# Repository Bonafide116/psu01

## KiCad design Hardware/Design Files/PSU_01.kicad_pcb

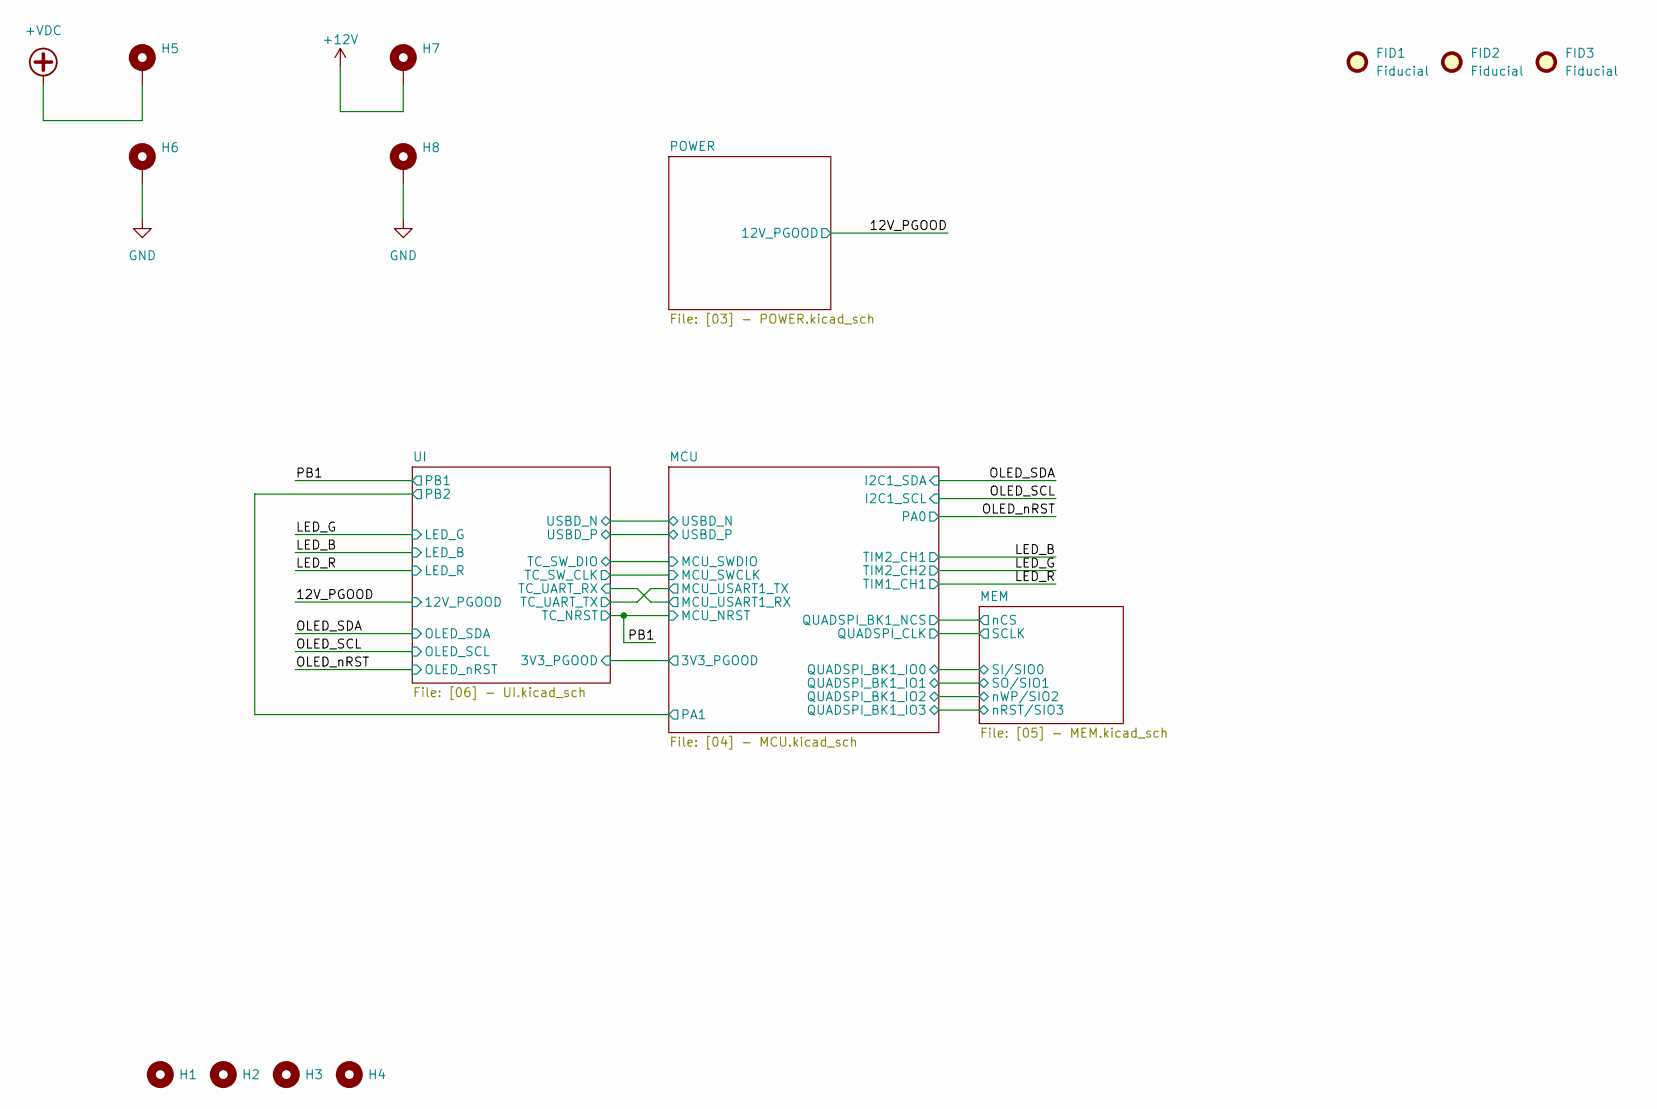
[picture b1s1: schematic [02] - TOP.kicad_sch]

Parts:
FID1, FID2, FID3: Fiducial; FID
H1, H2, H3, H4: MountingHole; MountingHole_3.5mm_Pad_Via
H5, H6, H7, H8: MountingHole_Pad; MountingHole_2.7mm_Pad

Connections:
+12V: H7.1; also elsewhere on the board
+VDC: H5.1; also elsewhere on the board
GND: H6.1, H8.1; also elsewhere on the board

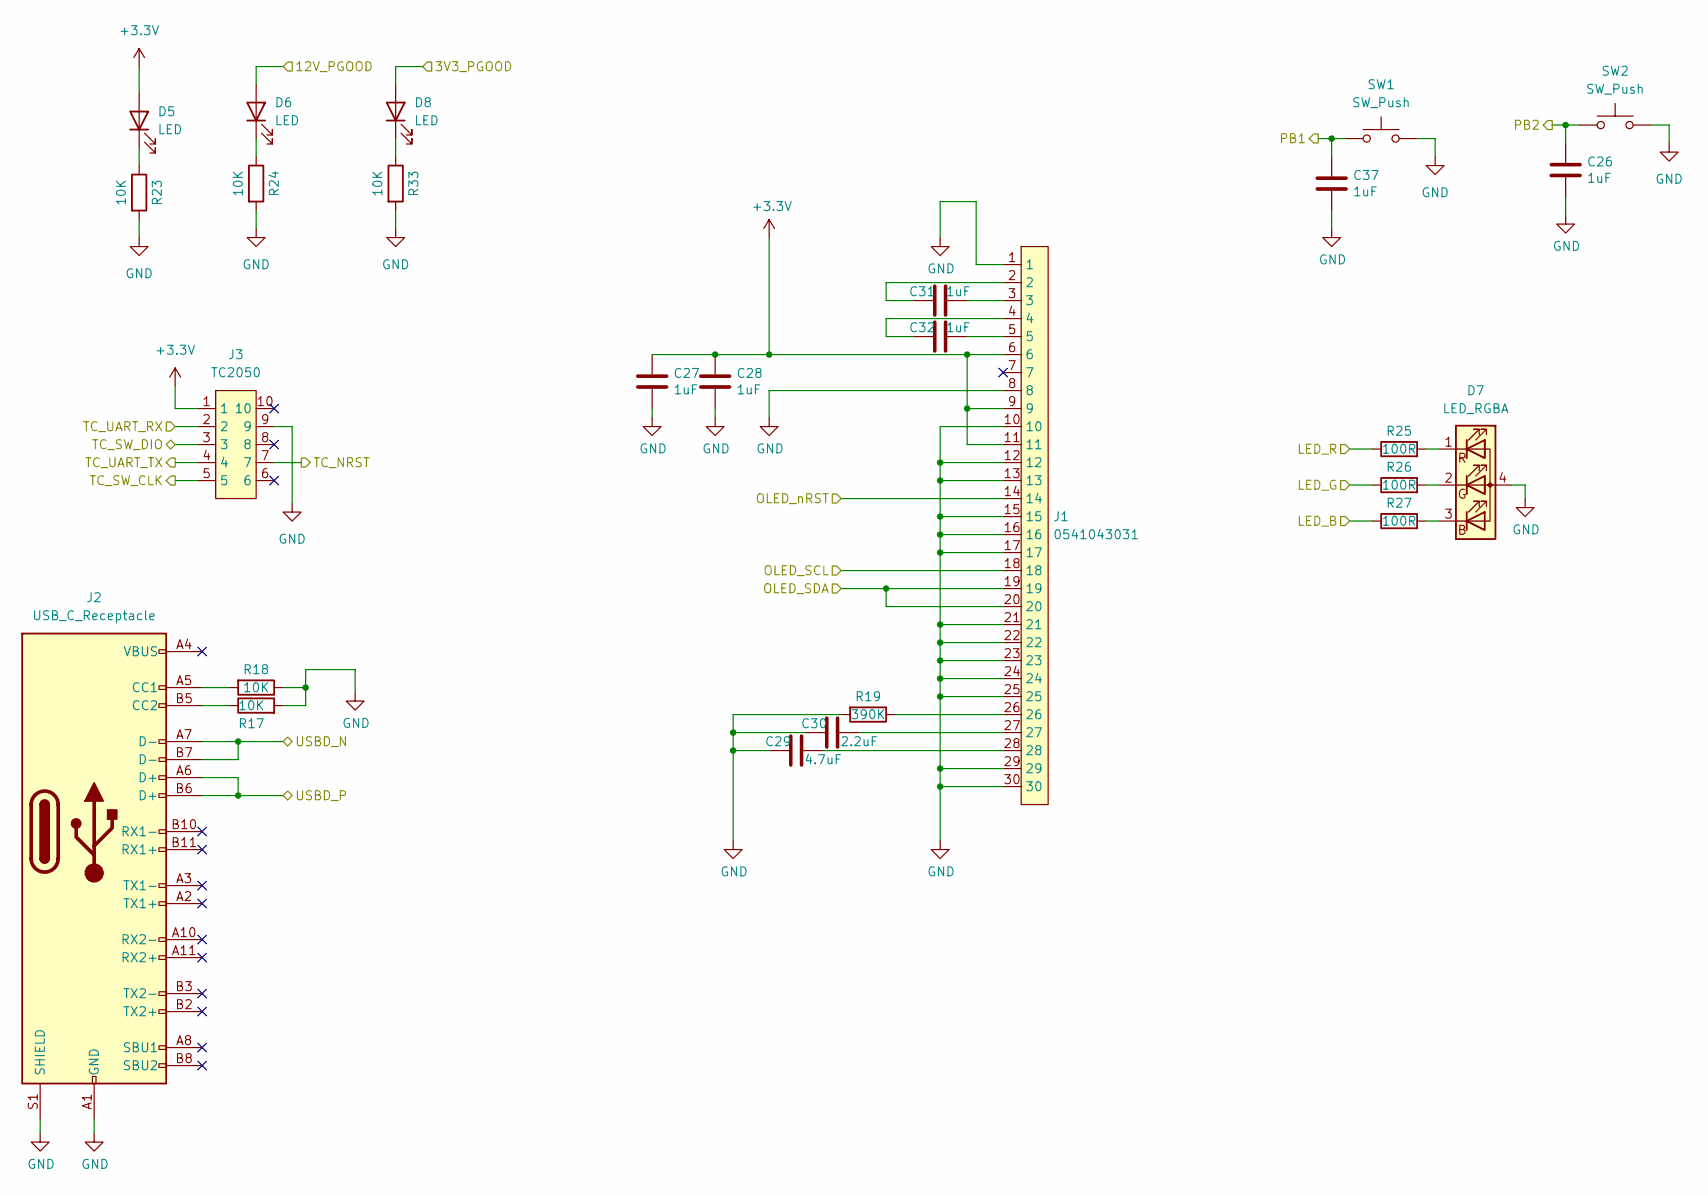
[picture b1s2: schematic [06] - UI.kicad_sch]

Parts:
C26, C27, C28, C31, C32, C37: 1uF; C_0603_1608Metric; Part Number CL10B105KP8NNNC
C29: 4.7uF; C_0603_1608Metric; Part Number CL10A475KO8NNNC
C30: 2.2uF; C_0603_1608Metric; Part Number CL10A225KO8NNNC
D5, D6, D8: LED; LED_0603_1608Metric
D7: LED_RGBA; LTST-C19HE1WT; Part Number LTST-C19HE1WT
J1: 0541043031; Part Number 0541043031
J2: USB_C_Receptacle; USB_C_Receptacle_Molex_105450-0101; Part Number 1054500101
J3: TC2050; Tag-Connect_TC2050-IDC-FP_2x05_P1.27mm_Vertical
R17, R18, R23, R24, R33: 10K; R_0603_1608Metric; Part Number RC0603FR-0710KL
R19: 390K; R_0603_1608Metric; Part Number RC0603FR-07390KL
R25, R26, R27: 100R; R_0603_1608Metric; Part Number RC0603FR-07100RL
SW1, SW2: SW_Push; SW_Push_1P1T_NO_Vertical_Wuerth_434133025816; Part Number 434133025816

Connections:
+3.3V: C27.2, C28.2, D5.2 (A), J1.6, J1.9, J1.11, J3.1; also elsewhere on the board
/TOP/12V_PGOOD: D6.2 (A); also elsewhere on the board
/TOP/LED_B: R27.1; also elsewhere on the board
/TOP/LED_G: R26.1; also elsewhere on the board
/TOP/LED_R: R25.1; also elsewhere on the board
/TOP/MCU/3V3_PGOOD: D8.2 (A); also elsewhere on the board
/TOP/MCU/MCU_SWCLK: J3.5; also elsewhere on the board
/TOP/MCU/MCU_SWDIO: J3.3; also elsewhere on the board
/TOP/MCU/MCU_USART1_RX: J3.2; also elsewhere on the board
/TOP/MCU/MCU_USART1_TX: J3.4; also elsewhere on the board
/TOP/MCU/PA1: C26.2, SW2.1; also elsewhere on the board
/TOP/MCU/USBD_N: J2.A7 (D-), J2.B7 (D-); also elsewhere on the board
/TOP/MCU/USBD_P: J2.A6 (D+), J2.B6 (D+); also elsewhere on the board
/TOP/OLED_SCL: J1.18; also elsewhere on the board
/TOP/OLED_SDA: J1.19, J1.20; also elsewhere on the board
/TOP/OLED_nRST: J1.14; also elsewhere on the board
/TOP/PB1: C37.2, J3.7, SW1.1; also elsewhere on the board
GND: C26.1, C27.1, C28.1, C29.2, C30.2, C37.1, D7.4 (A), J1.1, J1.8, J1.10, J1.12, J1.13, J1.15, J1.16, J1.17, J1.21, J1.22, J1.23, J1.24, J1.25, J1.29, J1.30, J2.A1 (GND), J2.A12 (GND), J2.B1 (GND), J2.B12 (GND), J2.S1 (SHIELD), J3.9, R17.2, R18.1, R19.2, R23.2, R24.2, R33.2, SW1.2, SW2.2; also elsewhere on the board
unnamed: C29.1, J1.28
unnamed: C30.1, J1.27
unnamed: C31.1, J1.3
unnamed: C31.2, J1.2
unnamed: C32.1, J1.5
unnamed: C32.2, J1.4
unnamed: D5.1 (K), R23.1
unnamed: D6.1 (K), R24.1
unnamed: D7.1 (RK), R25.2
unnamed: D7.2 (GK), R26.2
unnamed: D7.3 (BK), R27.2
unnamed: D8.1 (K), R33.1
unnamed: J1.26, R19.1
unnamed: J2.A5 (CC1), R18.2
unnamed: J2.B5 (CC2), R17.1

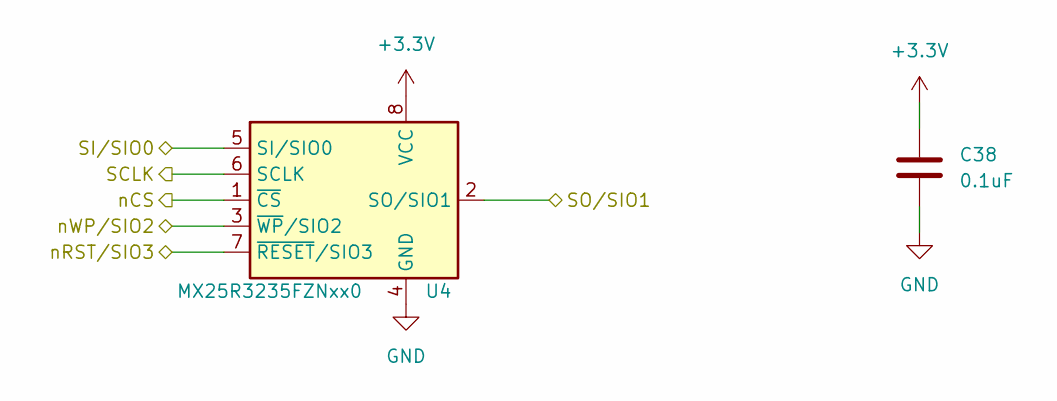
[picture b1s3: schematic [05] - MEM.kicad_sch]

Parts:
C38: 0.1uF; C_0603_1608Metric; Part Number CL10B104KB8NNNC
U4: MX25R3235FZNxx0; WSON-8-1EP_6x5mm_P1.27mm_EP3.4x4mm; Part Number MX25R3235FZNIL0

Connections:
+3.3V: C38.1, U4.8 (VCC); also elsewhere on the board
/TOP/MCU/QUADSPI_BK1_IO0: U4.5 (SI/SIO0); also elsewhere on the board
/TOP/MCU/QUADSPI_BK1_IO1: U4.2 (SO/SIO1); also elsewhere on the board
/TOP/MCU/QUADSPI_BK1_IO2: U4.3 (~WP/SIO2); also elsewhere on the board
/TOP/MCU/QUADSPI_BK1_IO3: U4.7 (~RESET/SIO3); also elsewhere on the board
/TOP/MCU/QUADSPI_BK1_NCS: U4.1 (~CS); also elsewhere on the board
/TOP/MCU/QUADSPI_CLK: U4.6 (SCLK); also elsewhere on the board
GND: C38.2, U4.4 (GND), U4.9 (GND); also elsewhere on the board

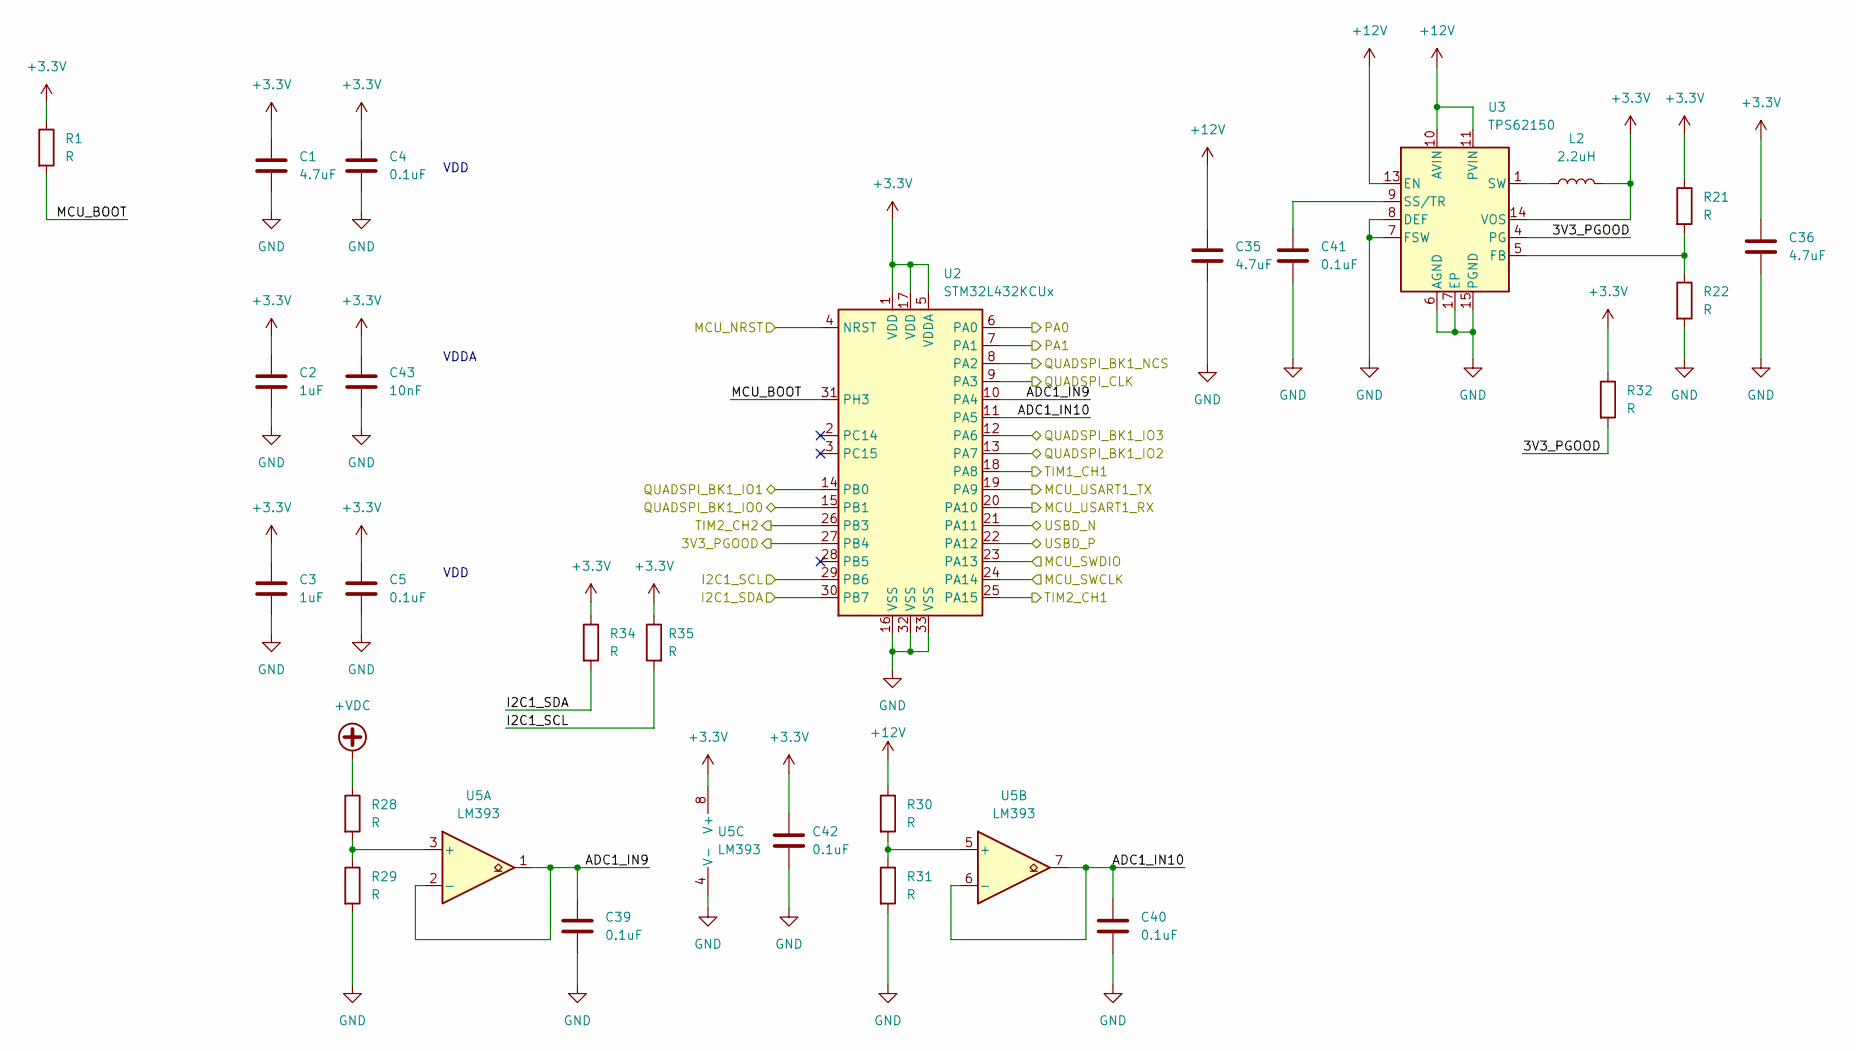
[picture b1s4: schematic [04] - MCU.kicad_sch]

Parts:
C1, C35, C36: 4.7uF; C_0805_2012Metric; Part Number CL21A475KAQNNNE
C2, C3: 1uF; C_0603_1608Metric; Part Number CL10B105KP8NNNC
C4, C5, C39, C40, C41, C42: 0.1uF; C_0603_1608Metric; Part Number CL10B104KB8NNNC
C43: 10nF; C_0603_1608Metric; Part Number CL10B103KB8NNNC
L2: 2.2uH; WE-XHMA; Part Number 78439344022
R1, R21, R22, R28, R29, R30, R31, R32, R34, R35: R; R_0603_1608Metric
U2: STM32L432KCUx; QFN-32-1EP_5x5mm_P0.5mm_EP3.45x3.45mm; Part Number STM32L432KCU6
U3: TPS62150; VQFN-16-1EP_3x3mm_P0.5mm_EP1.68x1.68mm; Part Number TPS62150RGTR
U5: LM393; SOIC-8_3.9x4.9mm_P1.27mm

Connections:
+3.3V: C1.1, C2.1, C3.1, C4.1, C5.1, C36.1, C42.1, C43.1, L2.2, R1.1, R21.1, R32.1, R34.1, R35.1, U2.1 (VDD), U2.5 (VDDA), U2.17 (VDD), U3.14 (VOS), U5.8 (V+); also elsewhere on the board
+12V: C35.1, R30.1, U3.10 (AVIN), U3.11 (PVIN), U3.12 (PVIN), U3.13 (EN); also elsewhere on the board
+VDC: R28.1; also elsewhere on the board
/TOP/LED_B: U2.25 (PA15); also elsewhere on the board
/TOP/LED_G: U2.26 (PB3); also elsewhere on the board
/TOP/LED_R: U2.18 (PA8); also elsewhere on the board
/TOP/MCU/3V3_PGOOD: R32.2, U2.27 (PB4), U3.4 (PG); also elsewhere on the board
/TOP/MCU/ADC1_IN9: C39.1, U2.10 (PA4), U5.1, U5.2 (-)
/TOP/MCU/ADC1_IN10: C40.1, U2.11 (PA5), U5.6 (-), U5.7
/TOP/MCU/MCU_BOOT: R1.2, U2.31 (PH3)
/TOP/MCU/MCU_SWCLK: U2.24 (PA14); also elsewhere on the board
/TOP/MCU/MCU_SWDIO: U2.23 (PA13); also elsewhere on the board
/TOP/MCU/MCU_USART1_RX: U2.20 (PA10); also elsewhere on the board
/TOP/MCU/MCU_USART1_TX: U2.19 (PA9); also elsewhere on the board
/TOP/MCU/PA1: U2.7 (PA1); also elsewhere on the board
/TOP/MCU/QUADSPI_BK1_IO0: U2.15 (PB1); also elsewhere on the board
/TOP/MCU/QUADSPI_BK1_IO1: U2.14 (PB0); also elsewhere on the board
/TOP/MCU/QUADSPI_BK1_IO2: U2.13 (PA7); also elsewhere on the board
/TOP/MCU/QUADSPI_BK1_IO3: U2.12 (PA6); also elsewhere on the board
/TOP/MCU/QUADSPI_BK1_NCS: U2.8 (PA2); also elsewhere on the board
/TOP/MCU/QUADSPI_CLK: U2.9 (PA3); also elsewhere on the board
/TOP/MCU/USBD_N: U2.21 (PA11); also elsewhere on the board
/TOP/MCU/USBD_P: U2.22 (PA12); also elsewhere on the board
/TOP/OLED_SCL: R35.2, U2.29 (PB6); also elsewhere on the board
/TOP/OLED_SDA: R34.2, U2.30 (PB7); also elsewhere on the board
/TOP/OLED_nRST: U2.6 (PA0); also elsewhere on the board
/TOP/PB1: U2.4 (NRST); also elsewhere on the board
GND: C1.2, C2.2, C3.2, C4.2, C5.2, C35.2, C36.2, C39.2, C40.2, C41.2, C42.2, C43.2, R22.2, R29.2, R31.2, U2.16 (VSS), U2.32 (VSS), U2.33 (VSS), U3.6 (AGND), U3.7 (FSW), U3.8 (DEF), U3.15 (PGND), U3.16 (PGND), U3.17 (EP), U5.4 (V-); also elsewhere on the board
unnamed: C41.1, U3.9 (SS/TR)
unnamed: L2.1, U3.1 (SW), U3.2 (SW), U3.3 (SW)
unnamed: R21.2, R22.1, U3.5 (FB)
unnamed: R28.2, R29.1, U5.3 (+)
unnamed: R30.2, R31.1, U5.5 (+)

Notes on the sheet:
VDD
VDDA

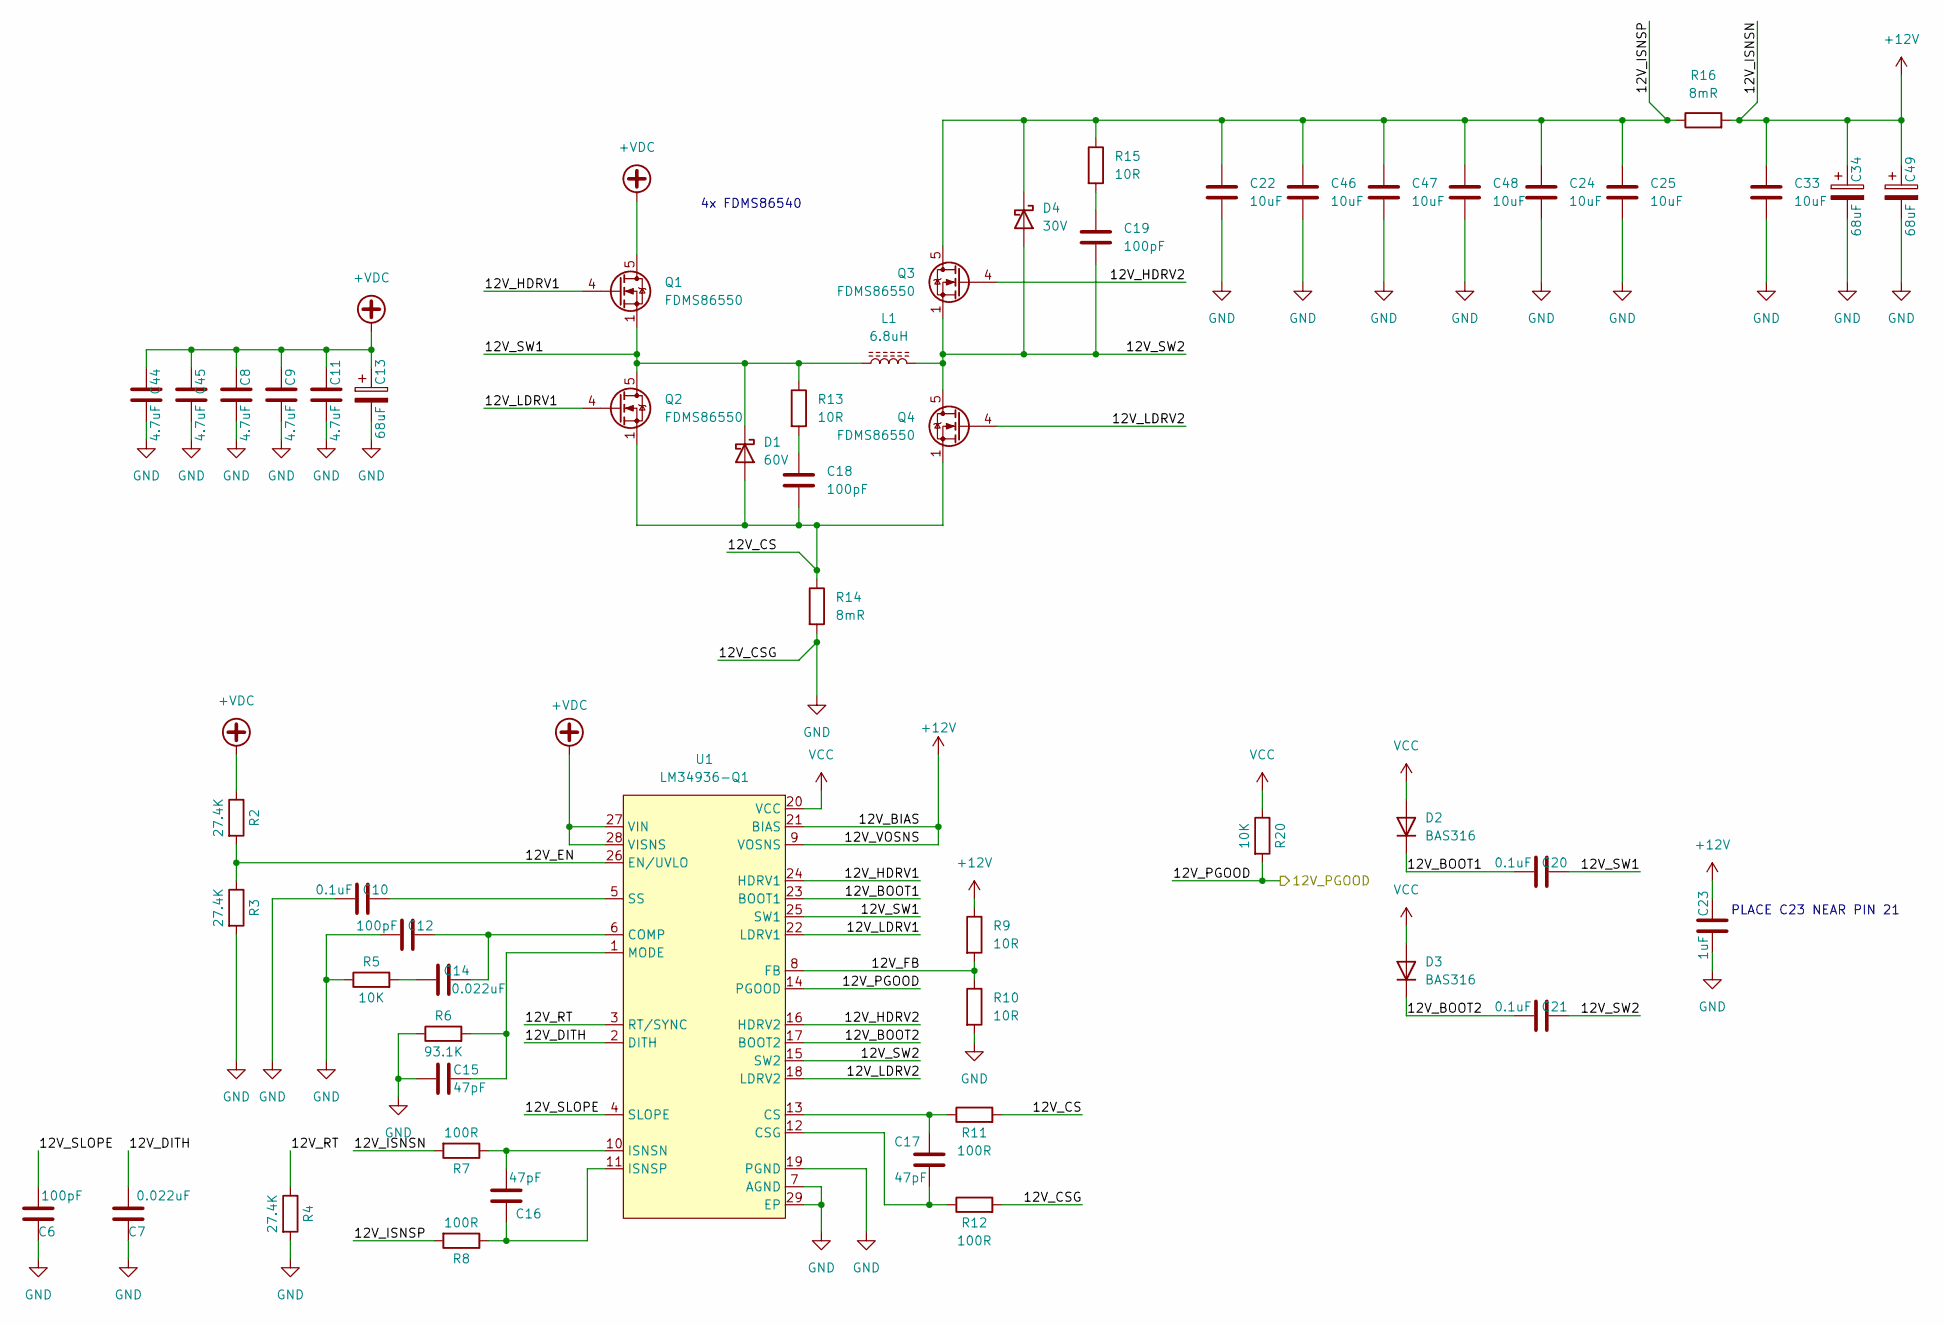
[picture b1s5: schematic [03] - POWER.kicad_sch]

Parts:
C6, C12, C18, C19: 100pF; C_0603_1608Metric; Part Number CL10C101JB8NNNC
C7, C14: 0.022uF; C_0603_1608Metric; Part Number CL10B223KB8WPNC
C8, C9, C44, C45: 4.7uF; C_1206_3216Metric; Part Number CL31A475KBHNNNE
C10, C20, C21: 0.1uF; C_0603_1608Metric; Part Number CL10B104KB8NNNC
C11: 4.7uF; C_0805_2012Metric; Part Number CL21A475KAQNNNE
C13, C34, C49: 68uF; CP_Elec_10x10
C15, C16, C17: 47pF; C_0603_1608Metric; Part Number CL10C470JB8NNNC
C22, C24, C25, C33, C46, C47, C48: 10uF; C_1206_3216Metric; Part Number CL31A106MBHNNNE
C23: 1uF; C_0603_1608Metric; Part Number CL10B105KP8NNNC
D1: 60V; D_SMC; Part Number B560CQ-13-F
D2, D3: BAS316; D_SOD-323
D4: 30V; D_SMC; Part Number B530C-13-F
L1: 6.8uH; IND_SER20xx; Part Number 74436410470
Q1, Q2, Q3, Q4: FDMS86550; TDSON-8-1; Part Number FDMS86540
R2, R3, R4: 27.4K; R_0603_1608Metric; Part Number RC0603FR-0727K4L
R5, R20: 10K; R_0603_1608Metric; Part Number RC0603FR-0710KL
R6: 93.1K; R_0603_1608Metric; Part Number RT0603BRD0793K1L
R7, R8, R11, R12: 100R; R_0603_1608Metric; Part Number RC0603FR-07100RL
R9, R10, R13, R15: 10R; R_0603_1608Metric; Part Number RC0603FR-0710RL
R14, R16: 8mR; RES_3015-WIDE
U1: LM34936-Q1; QFN-28_5x4; Part Number LM34936-Q1

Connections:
+12V: C23.2, C33.1, C34.1, C49.1, R7.2, R9.1, R16.2, U1.9 (VOSNS), U1.21 (BIAS); also elsewhere on the board
+VDC: C8.2, C9.2, C11.2, C13.1, C44.2, C45.2, Q1.5 (D), R2.1, U1.27 (VIN), U1.28 (VISNS); also elsewhere on the board
/TOP/12V_PGOOD: R20.2, U1.14 (PGOOD); also elsewhere on the board
/TOP/POWER/12V_BOOT1: C20.1, D2.1 (K), U1.23 (BOOT1)
/TOP/POWER/12V_BOOT2: C21.1, D3.1 (K), U1.17 (BOOT2)
/TOP/POWER/12V_CS: C18.2, D1.2 (A), Q2.1 (S), Q2.2 (S), Q2.3 (S), Q4.1 (S), Q4.2 (S), Q4.3 (S), R11.2, R14.1
/TOP/POWER/12V_DITH: C7.2, U1.2 (DITH)
/TOP/POWER/12V_EN: R2.2, R3.1, U1.26 (EN/UVLO)
/TOP/POWER/12V_FB: R9.2, R10.1, U1.8 (FB)
/TOP/POWER/12V_HDRV1: Q1.4 (G), U1.24 (HDRV1)
/TOP/POWER/12V_HDRV2: Q3.4 (G), U1.16 (HDRV2)
/TOP/POWER/12V_ISNSP: C22.1, C24.1, C25.1, C46.1, C47.1, C48.1, D4.1 (K), Q3.5 (D), R8.2, R15.1, R16.1
/TOP/POWER/12V_LDRV1: Q2.4 (G), U1.22 (LDRV1)
/TOP/POWER/12V_LDRV2: Q4.4 (G), U1.18 (LDRV2)
/TOP/POWER/12V_RT: R4.1, U1.3 (RT/SYNC)
/TOP/POWER/12V_SLOPE: C6.2, U1.4 (SLOPE)
/TOP/POWER/12V_SW1: C20.2, D1.1 (K), L1.1, Q1.1 (S), Q1.2 (S), Q1.3 (S), Q2.5 (D), R13.1, U1.25 (SW1)
/TOP/POWER/12V_SW2: C19.2, C21.2, D4.2 (A), L1.2, Q3.1 (S), Q3.2 (S), Q3.3 (S), Q4.5 (D), U1.15 (SW2)
GND: C6.1, C7.1, C8.1, C9.1, C10.1, C11.1, C12.1, C13.2, C15.2, C22.2, C23.1, C24.2, C25.2, C33.2, C34.2, C44.1, C45.1, C46.2, C47.2, C48.2, C49.2, R3.2, R4.2, R5.1, R6.1, R10.2, R12.2, R14.2, U1.7 (AGND), U1.19 (PGND), U1.29 (EP); also elsewhere on the board
unnamed: C10.2, U1.5 (SS)
unnamed: C12.2, C14.2, U1.6 (COMP)
unnamed: C14.1, R5.2
unnamed: C15.1, R6.2, U1.1 (MODE)
unnamed: C16.1, R8.1, U1.11 (ISNSP)
unnamed: C16.2, R7.1, U1.10 (ISNSN)
unnamed: C17.1, R11.1, U1.13 (CS)
unnamed: C17.2, R12.1, U1.12 (CSG)
unnamed: C18.1, R13.2
unnamed: C19.1, R15.2
VCC: D2.2 (A), D3.2 (A), R20.1, U1.20 (VCC)

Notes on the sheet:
4x FDMS86540
PLACE C23 NEAR PIN 21

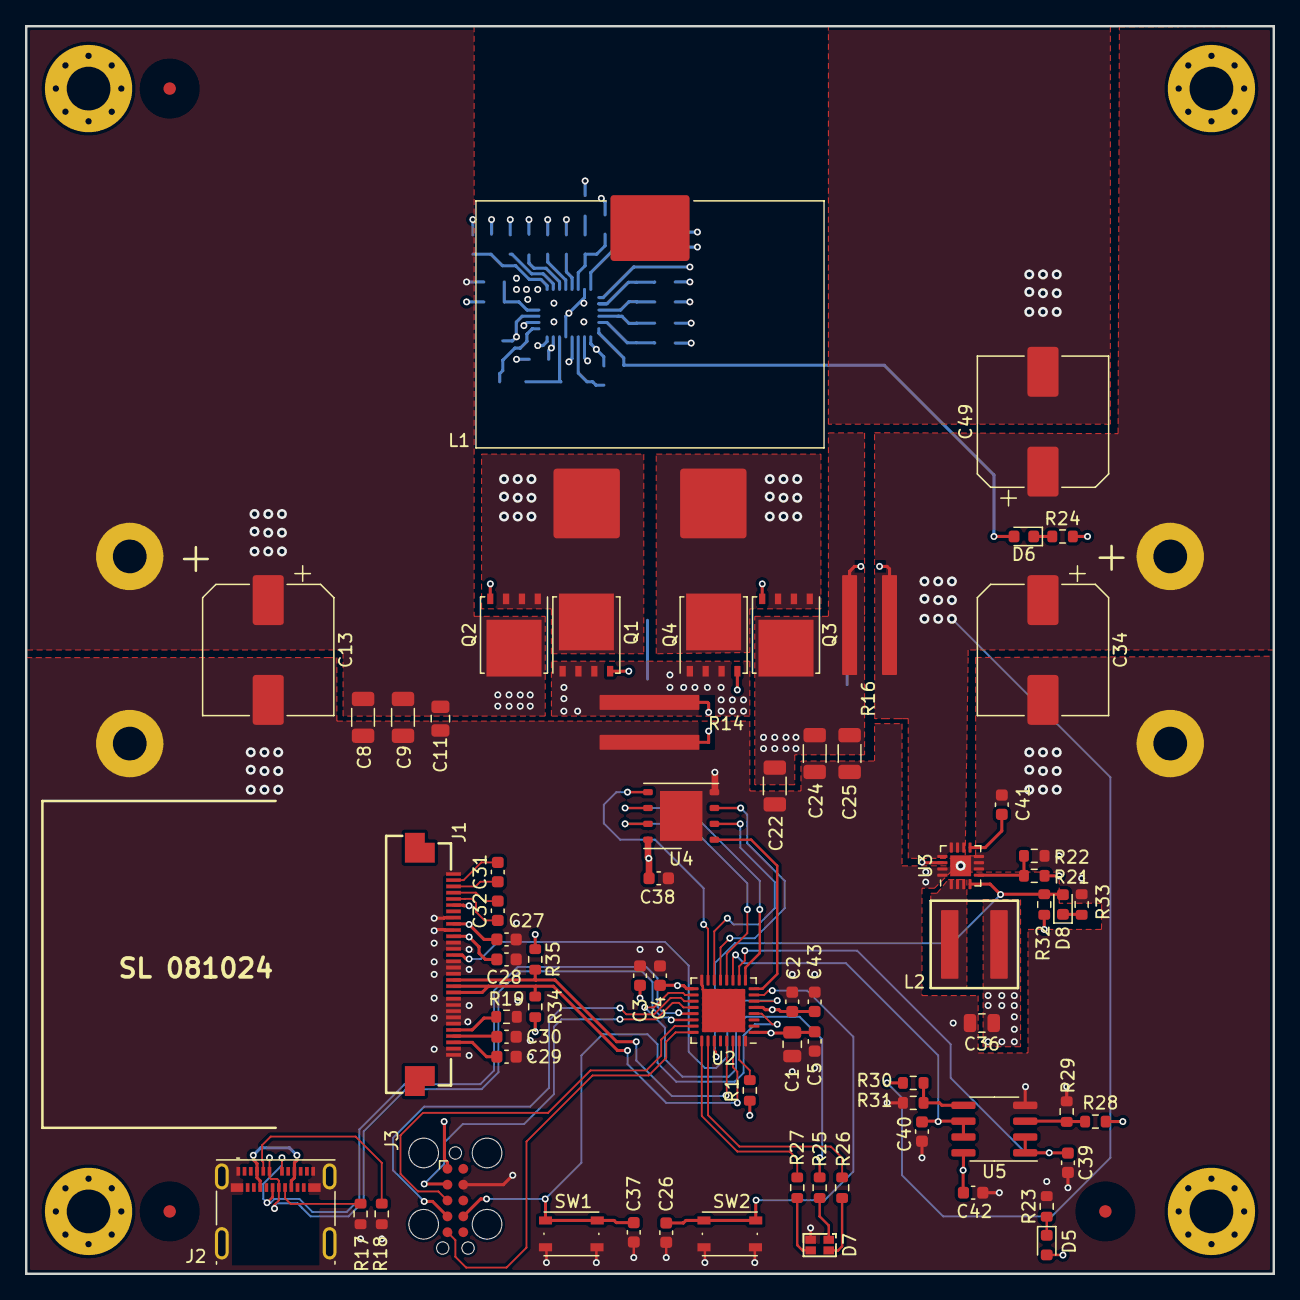
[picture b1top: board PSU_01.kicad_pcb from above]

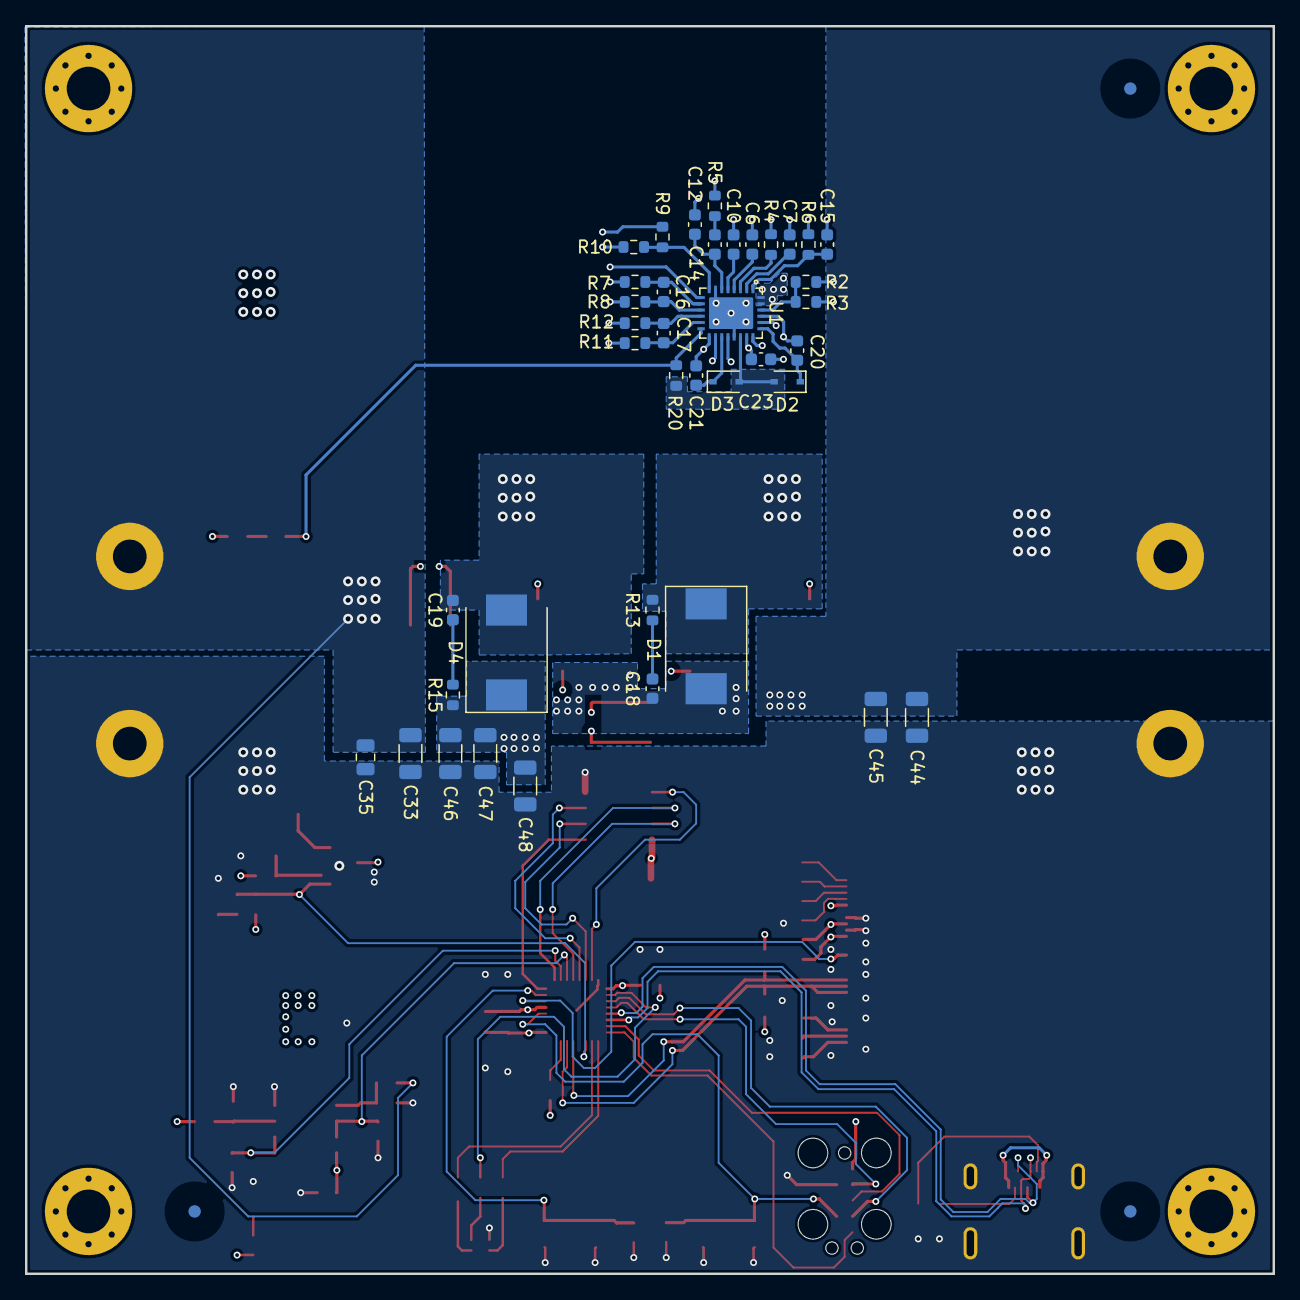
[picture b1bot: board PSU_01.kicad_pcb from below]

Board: 4 copper layers, 100.0 x 100.0 mm, 119 parts (39 on the bottom side), 75 nets.

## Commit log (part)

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2024-06-07 initial commit; schematic progress;
